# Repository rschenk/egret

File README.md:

# Egret

A 36 key Choc-spaced monoblock keyboard that's wireless compatible, hot swappable, gasket mounted, and very thin. Inspired by the [chocV](https://github.com/brickbots/chocV) and [Horizon](https://github.com/skarrmann/horizon/).

The Egret's bottom plate has cutouts for the hotswap sockets, essentially the thinnest board possible with hotswap sockets. Silicone gaskets sandwiching both sides of the PCB dampen sounds and vibrations. The entire bottom is covered with rubber sheet so you can use it right on your laptop keys if you're so inclined!

## Features

* Choc hotswap sockets with Choc spacing
* Gasket mounted
* On/off slider switch and JST plug for battery power
* Totally flat bottom, so you can put it right on top of your laptop keyboard and Miyoku on the go
* Optional LED underglow for wired mode, if underglow is your thing. It's very much my thing
* Two bottom plate options: lowpro mode for the thinnest board physically possible, or glowpro mode for epic underglow at the expense of a couple mm of thickess.

## Wicked Thin and Flat

The bottom plate is cut out to accomodate the hotswap sockets, making it about as thin as is physically possible to make a hotswap board. The entire bottom is intended to be covered with rubber, sililicone, EVA, etc, so you can put it down on right over your laptop's keys. Yes this actually works and is useable! 

## Build Guide

There are two ways to build it, with LED underglow (glow-profile case) and without (low profile case). The LED version requires a different bottom plate which is 1.5mm taller than the low-profile version, but everything else is the same between them—same PCB, top plate, gaskets, etc. _Either_ version can be used with bluetooth! Obviously running the LEDs will drain your battery much faster, but it's easy to have  the best of both worlds by configuring ZMK to automatically enable LEDs when plugged into USB and disable them when on battery power.

* Build guide for [low profile version](./docs/rev1/build_guide_lowpro_rev1.md) (no LEDs)
* Build guide for [glow profile version](./docs/rev1/build_guide_glowpro_rev1.md) (with LED underglow)

## Firmware

### QMK

Egret is not in the main QMK repo yet (or probably ever) but it's easy to add to your local.
Assuming you already have QMK set up on your computer, copy the contents of `./firmware/qmk` to `qmk_firmware/keyboards/egret`. There is a very minimal basic keymap for you to start with.

```sh
cp -R ./firmware/qmk /path/to/qmk_firmware/keyboards/egret
cd !$
cp -R keymaps/default keymaps/your-github-username
```

### ZMK

Egret is not in the main ZMK repo but it's easy to add. Assuming you already have a zmk-config setp already, copy the contents of `./firmware/zmk` to `zmk-config/config/boards/shields/egret`, then make the usual setup. There is a basic minimal keymap for you to start with.

```sh
cp -R ./firmware/zmk /path/to/zmk-config/config/boards/shields/egret
cd /path/to/zmk-config/config
cp boards/shields/egret/egret.keymap .
touch egret.conf
```

## Tweak Your Own With Ergogen

This board is generated with the amazing ergogen tool, then post-processed with KiCad and vector graphics drawing tools. I used several custom footrpints to pull off the "horizon construction" on the bottom plate. Since ergogen does not currently support adding footprints at runtime, I Dockerized it and copied my footprints into the image. The Dockerfile lives in `ergogen/container` and can be run with a little wrapper script I wrote in `ergogen/bin/ergogen`. 

To generate the board (which you should not need to unless you want to change something):

```shell
$ cd ergogen
$ bin/ergogen egret.yml
```

If you decide to edit a footprint, you'll need to remove the image and rebuild it.
```shell
# Only if you modify a footprint, rebuild the image like so:
$ docker image rm -f ergogen-egret && bin/ergogen egret.yml
```

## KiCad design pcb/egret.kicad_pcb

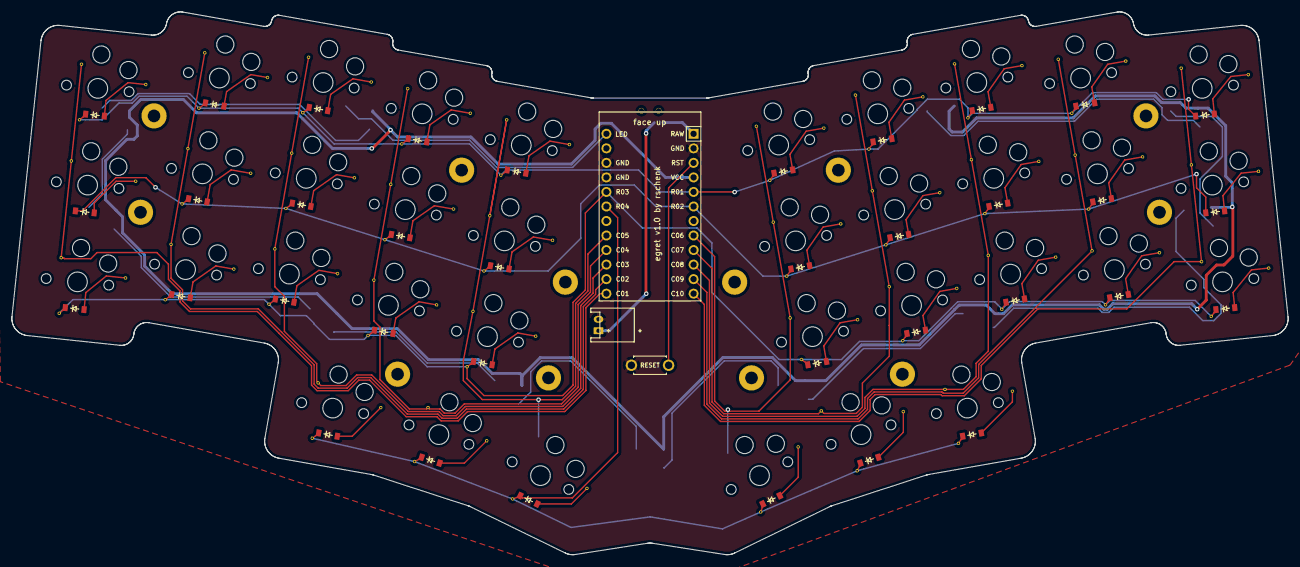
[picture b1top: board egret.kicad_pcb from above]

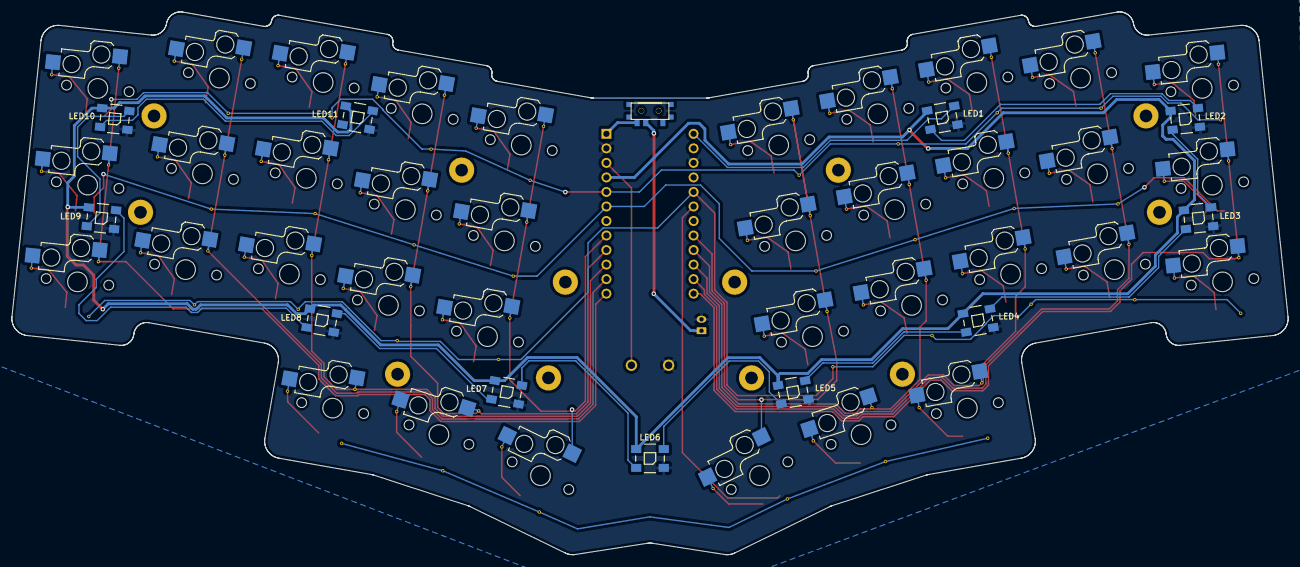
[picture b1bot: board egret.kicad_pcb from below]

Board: 2 copper layers, 223.1 x 94.9 mm, 100 parts (11 on the bottom side), 66 nets.

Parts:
B1: ResetSW_1side
D1, D2, D3, D4, D5, D6, D7, D8, D9, D10, D11, D12, D13, D14, D15, D16, D17, D18, D19, D20, D21, D22, D23, D24, D25, D26, D27, D28, D29, D30, D31, D32, D33, D34, D35, D36: ComboDiode
JST1: JST_PH_S2B-PH-K_02x2.00mm_Angled
LED1, LED2, LED3, LED4, LED5, LED6, LED7, LED8, LED9, LED10, LED11: VAL**; WS2812B
MCU1: ProMicro
PAD1: ProMicroPadCutouts
PAD2, PAD3, PAD4, PAD5, PAD6, PAD7, PAD8, PAD9, PAD10, PAD11, PAD12, PAD13: MountingHole_2.2mm_M2_Pad
S1, S2, S3, S4, S5, S6, S7, S8, S9, S10, S11, S12, S13, S14, S15, S16, S17, S18, S19, S20, S21, S22, S23, S24, S25, S26, S27, S28, S29, S30, S31, S32, S33, S34, S35, S36: PG1350
T1: SPDT_C128955

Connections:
BAT_POS: JST1.1, T1.2
GND: B1.2, JST1.2, LED1.3, LED2.3, LED3.3, LED4.3, LED5.3, LED6.3, LED7.3, LED8.3, LED9.3, LED10.3, LED11.3, MCU1.2, MCU1.15, MCU1.16
L2: LED1.2, LED2.4
L3: LED2.2, LED3.4
L4: LED3.2, LED4.4
L5: LED4.2, LED5.4
L6: LED5.2, LED6.4
L7: LED6.2, LED7.4
L8: LED7.2, LED8.4
L9: LED8.2, LED9.4
L10: LED9.2, LED10.4
L11: LED10.2, LED11.4
RAW: MCU1.1, T1.3
RST: B1.1, MCU1.3
VCC: LED1.1, LED2.1, LED3.1, LED4.1, LED5.1, LED6.1, LED7.1, LED8.1, LED9.1, LED10.1, LED11.1, MCU1.4
col1: MCU1.24, S1.1, S1.3, S1.5, S2.1, S2.3, S2.5, S3.1, S3.3, S3.5
col2: MCU1.23, S4.1, S4.3, S4.5, S5.1, S5.3, S5.5, S6.1, S6.3, S6.5
col3: MCU1.22, S7.1, S7.3, S7.5, S8.1, S8.3, S8.5, S9.1, S9.3, S9.5, S16.1, S16.3, S16.5
col4: MCU1.21, S10.1, S10.3, S10.5, S11.1, S11.3, S11.5, S12.1, S12.3, S12.5, S17.1, S17.3, S17.5
col5: MCU1.20, S13.1, S13.3, S13.5, S14.1, S14.3, S14.5, S15.1, S15.3, S15.5, S18.1
col6: MCU1.8, S31.1, S31.3, S31.5, S32.1, S32.3, S32.5, S33.1, S33.3, S33.5, S36.1
col7: MCU1.9, S28.1, S28.3, S28.5, S29.1, S29.3, S29.5, S30.1, S30.3, S30.5, S35.1, S35.3, S35.5
col8: MCU1.10, S25.1, S25.3, S25.5, S26.1, S26.3, S26.5, S27.1, S27.3, S27.5, S34.1, S34.3, S34.5
col9: MCU1.11, S22.1, S22.3, S22.5, S23.1, S23.3, S23.5, S24.1, S24.3, S24.5
col10: MCU1.12, S19.1, S19.3, S19.5, S20.1, S20.3, S20.5, S21.1, S21.3, S21.5
home_thumb: D17.2, S17.2, S17.4, S17.6
index_bottom: D10.2, S10.2, S10.4, S10.6
index_home: D11.2, S11.2, S11.4, S11.6
index_top: D12.2, S12.2, S12.4, S12.6
inner_bottom: D13.2, S13.2, S13.4, S13.6
inner_home: D14.2, S14.2, S14.4, S14.6
inner_top: D15.2, S15.2, S15.4, S15.6
led: LED1.4, MCU1.13
middle_bottom: D7.2, S7.2, S7.4, S7.6
middle_home: D8.2, S8.2, S8.4, S8.6
middle_top: D9.2, S9.2, S9.4, S9.6
mirror_home_thumb: D35.2, S35.2, S35.4, S35.6
mirror_index_bottom: D28.2, S28.2, S28.4, S28.6
mirror_index_home: D29.2, S29.2, S29.4, S29.6
mirror_index_top: D30.2, S30.2, S30.4, S30.6
mirror_inner_bottom: D31.2, S31.2, S31.4, S31.6
mirror_inner_home: D32.2, S32.2, S32.4, S32.6
mirror_inner_top: D33.2, S33.2, S33.4, S33.6
mirror_middle_bottom: D25.2, S25.2, S25.4, S25.6
mirror_middle_home: D26.2, S26.2, S26.4, S26.6
mirror_middle_top: D27.2, S27.2, S27.4, S27.6
mirror_pinky_bottom: D19.2, S19.2, S19.4, S19.6
mirror_pinky_home: D20.2, S20.2, S20.4, S20.6
mirror_pinky_top: D21.2, S21.2, S21.4, S21.6
mirror_reachy_thumb: D36.2, S36.2, S36.4, S36.6
mirror_ring_bottom: D22.2, S22.2, S22.4, S22.6
mirror_ring_home: D23.2, S23.2, S23.4, S23.6
mirror_ring_top: D24.2, S24.2, S24.4, S24.6
mirror_tucky_thumb: D34.2, S34.2, S34.4, S34.6
pinky_bottom: D1.2, S1.2, S1.4, S1.6
pinky_home: D2.2, S2.2, S2.4, S2.6
pinky_top: D3.2, S3.2, S3.4, S3.6
reachy_thumb: D18.2, S18.2, S18.4, S18.6
ring_bottom: D4.2, S4.2, S4.4, S4.6
ring_home: D5.2, S5.2, S5.4, S5.6
ring_top: D6.2, S6.2, S6.4, S6.6
row1: D3.1, D3.3, D3.4, D6.1, D6.3, D6.4, D9.1, D9.3, D9.4, D12.1, D12.3, D12.4, D15.1, D15.3, D15.4, D21.1, D24.1, D24.3, D24.4, D27.1, D27.3, D27.4, D30.1, D30.3, D30.4, D33.1, D33.3, D33.4, MCU1.5
row2: D2.1, D5.1, D5.3, D5.4, D8.1, D8.3, D8.4, D11.1, D11.3, D11.4, D14.1, D14.3, D14.4, D20.1, D23.1, D23.3, D23.4, D26.1, D26.3, D26.4, D29.1, D29.3, D29.4, D32.1, D32.3, D32.4, MCU1.6
row3: D1.1, D1.3, D1.4, D4.1, D4.3, D4.4, D7.1, D7.3, D7.4, D10.1, D10.3, D10.4, D13.1, D13.3, D13.4, D19.1, D19.3, D19.4, D22.1, D22.3, D22.4, D25.1, D25.3, D25.4, D28.1, D28.3, D28.4, D31.1, D31.3, D31.4, MCU1.17
row4: D16.1, D16.3, D16.4, D17.1, D17.3, D17.4, D18.1, D18.3, D18.4, D34.1, D34.3, D34.4, D35.1, D35.3, D35.4, D36.1, D36.3, D36.4, MCU1.18
tucky_thumb: D16.2, S16.2, S16.4, S16.6

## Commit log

2022-09-13 Create LICENSE
2022-09-13 Flesh out readme a bit
2022-09-13 v1.0 pcb design, gitignore
2022-09-14 Subtract soldermask from silkscreen in gerbers
2022-09-23 Subtract mask from silkscreens
2022-09-23 Bigger standoff clearance on top plate
2022-10-06 Add firmware
2022-10-06 Power switch cutout for glowpro bottom plate
2022-10-18 Build guide for Low-Pro rev1
2022-10-18 Glow-Pro rev1 build guide
2022-12-02 Flesh out readme
2022-12-02 Relative image paths
2022-12-02 Add vs Fifi pic
2023-05-31 small documentation change
2023-06-30 Add underglow config for Nice Nano
2023-07-19 Fix nice nano zmk board config
